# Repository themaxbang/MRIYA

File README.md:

# MRIYA
**MRIYA** (Ukrainian for «Dream») is a 42-key column-staggered split keyboard based on [Corne Cherry v.3.0.1](https://github.com/foostan/crkbd)

## Features
- Design optimized for wireless
- Updated thumb cluster (inspired by [Jian](https://github.com/KGOH/Jian-Info))
- Reset buttons
- Native nice!view support
- Updated column stagger
- 3DP bumper case (inspired by [Dao Choc BLE](https://github.com/yumagulovrn/dao-choc-ble))
- CNC plates
- BSI-10H Slide Switches
- Molex PicoBlade 1.25mm connectors
- LiPo Battery 301230/301645 support
- No-Solder Spring Headers support
- No LEDs
- Hotswap MX
- ZMK support

## PCB
<table align="center">
    <tr>
        <td align="left">Software</td>
        <td align="left"><a href="https://www.kicad.org/">KiCad 9.0.7 Stable</a></td>
    </tr>
    <tr>
        <td align="left">Silkscreen font</td>
        <td align="left"><a href="https://fonts.google.com/specimen/Roboto">Roboto</a> | <a href="https://fonts.google.com/specimen/Roboto+Condensed">Roboto condensed</a></td>
    </tr>
    <tr>
        <td align="left">Bird logo</td>
        <td align="left"><a href="https://pngtree.com/freepng/minimalist-bird-logo_4124682.html">pngtree.com</a></td>
    </tr>
    <tr>
        <td align="left">PCB Art</td>
        <td align="left"> Olga Rai <a href="https://www.shutterstock.com/g/OlgaRai">Shutterstock</a> | <a href="https://stock.adobe.com/contributor/209778624/olga-rai">Adobe Stock</a></td>
    </tr>
</table>

#### <div align="center">Top<div>
| 
 ---- | -----  

#### <div align="center">Bottom<div>
|   
 ---- | -----  

## PCB Plates
<table align="center">
    <tr>
        <td align="left">Logo font</td>
        <td align="left"><a href="https://fontbundles.net/integritype-studio/1610789-william-narasi-calligraphy-font">William Narasi</a></td>
    </tr>
</table>

|   
 ---- | -----

## 3D Printed Bumper Case
#### <div align="center">FDM<div>
|
 ---- | -----

## Bill of Materials
Reference|Name|Qty|LCSC|AliExpess
 ------- | ------- | ------- | ------- | ------- 
U1, U2 | Microcontroller: [nRFMicro](https://github.com/joric/nrfmicro) / SuperMini nRF52840 / nice!nano | 2 | --- | [AliExpress](https://aliexpress.com/item/1005006282506884.html?sku_id=12000036599296319)
SW1-SW42 | Kailh Hotswap Socket CPG151101S11 | 42 | [LCSC](https://www.lcsc.com/product-detail/Mechanical-Keyboard-Shaft_span-style-background-color-ff0-Kailh-span-CPG151101S11-16_C5156480.html) | [AliExpress](https://aliexpress.com/item/1005007639688349.html?sku_id=12000041605806628)
D1-D42 | Diode 1N4148W (SOD-123) | 42 | [LCSC](https://www.lcsc.com/product-detail/Switching-Diodes_JSMSEMI-1N4148W_C917030.html) | [AliExpess](https://aliexpress.com/item/1005008224039255.html?sku_id=12000044288109815)
PSW1, PSW2 | Power Switch SUNGMUN BSI-10H | 2 | [LCSC](https://www.lcsc.com/product-detail/Slide-Switches_SM-Switch-BSI-10H_C5775777.html) | [AliExpress](https://aliexpress.com/item/1005006561513178.html?sku_id=12000037678382032)
RSW1, RSW2 | Reset Button TC-1109-C-A (4.5x4.5x**5.5**mm) 4pin DIP | 2 | [LCSC](https://www.lcsc.com/product-detail/Tactile-Switches_XKB-Connectivity-TC-1109-C-A_C561500.html) | [AliExpress](https://aliexpress.com/item/1005001629344310.html?sku_id=12000016890022339)
J1, J2 | Nice!view display [optional] | 2 | --- | [AliExpess](https://aliexpress.com/item/1005007972384358.html?sku_id=12000043094547978)
J3, J4 | Molex PicoBlade 532610271 connector | 2 | [LCSC](https://www.lcsc.com/product-detail/Wire-To-Board-Wire-To-Wire-Connector_MOLEX-532610271_C189700.html) | [AliExpress](https://aliexpress.com/item/1005004425197503.html?sku_id=12000029142536237)
--- | Socket PH5 12pin (Female header) pitch 2.54mm | 4 | --- | [AliExpress](https://aliexpress.com/item/1005006055026707.html?sku_id=12000037525939024)
--- | Socket PH5 5pin (Female header) pitch 2.54mm | 2 | --- | [AliExpress](https://aliexpress.com/item/1005006055026707.html?sku_id=12000037525939018)
--- | LiPo Battery 301230 | 2 | --- | [AliExpress](https://aliexpress.com/item/1005008151618452.html?sku_id=12000044007992383)
--- | LiPo Battery 301645 (Mounts underneath the PCB. During assembly, you must trim the PH5 sockets and power switches legs flush with the PCB using a special template) [optional] | 2 | --- | [AliExpress](https://aliexpress.com/item/32822552643.html?sku_id=64950436890)
--- | Jst Connector 1.25mm Dual Head Wire Cable 2 Pin Female Plug [optional] | 2 | --- | [AliExpress](https://aliexpress.com/item/1005006000774395.html?sku_id=12000035250620558)
--- | Silicone Bumpers 8x2mm (for Classic case or CNC plates) | 12 | --- | [AliExpress](https://aliexpress.com/item/1005005467943079.html?sku_id=12000033199265741)
--- | Silicone Bumpers 8x1.5mm (for FR4 plates) | 12 | --- | [AliExpress](https://aliexpress.com/item/1005002478823169.html?sku_id=12000038015770755)
--- | Brass Round Standoff Spacer Female M2 10mm | 4 | --- | [AliExpress](https://aliexpress.com/item/1005002979083511.html?sku_id=12000023043529034)
--- | Brass Round Standoff Spacer Female M2 7mm | 8 | --- | [AliExpress](https://aliexpress.com/item/1005002979083511.html?sku_id=12000023043529031)
--- | Brass Round Standoff Spacer Female M2 6mm (for Classic case 301230 + FR4 plates) | 8 | --- | [AliExpress](https://aliexpress.com/item/1005002979083511.html?sku_id=12000023043529030)
--- | M3 ABS Nylon Round Standoff Spacer 3.5mm | 12 | --- | [AliExpress](https://aliexpress.com/item/1005004162177818.html?sku_id=12000028239766646)
--- | M3 Black ABS Non-Threaded Hollowed Nylon Spacer 5mm [optional] | 4 | --- | [AliExpress](https://aliexpress.com/item/1005006120526666.html?sku_id=12000035843885709)
--- | M2 Stainless Steel Torx Six-Lobe Ultra Thin Head Screw 4mm | 24 | --- | [AliExpress](https://aliexpress.com/item/1005002461101939.html?sku_id=12000025423430581)
--- | M2 Stainless Steel Torx Head Flat Countersunk Screw 8mm (for Classic case + FDM plates) | 12 | --- | [AliExpress](https://aliexpress.com/item/1005007404555871.html?sku_id=12000040603875540)
--- | M2 Stainless Steel Torx Head Flat Countersunk Screw 5mm (for Classic case + FR4 plates) | 12 | --- | [AliExpress](https://aliexpress.com/item/1005007404555871.html?sku_id=12000040603875538)
--- | M2 Grade 12.9 Insert Torx Screw 5mm (for CNC covers) [optional] | 4 | --- | [AliExpress](https://aliexpress.com/item/4000498337202.html?sku_id=10000002274132371)
--- | М2 (OD 3.2mm) Brass Thread Heat Insert (for FDM plates and covers) length 3mm | 16 | --- | [AliExpress](https://aliexpress.com/item/1005006161392792.html?sku_id=12000036051013760)

## Firmware
You can use any firmware compatible with the Corne keyboard.
[ZMK Config](https://github.com/themaxbang/mriya-zmk-config) for the MRIYA

## Inspiration
- [Corne](https://github.com/foostan/crkbd) | [Corne Ultralight](https://github.com/petejohanson/crkbd/tree/board/corne-ultralight)
- [Jian](https://github.com/KGOH/Jian-Info)
- [Chocofi](https://github.com/pashutk/chocofi) | [Fifi](https://github.com/raychengy/fifi_split_keeb)
- [Dao Choc BLE](https://github.com/yumagulovrn/dao-choc-ble)

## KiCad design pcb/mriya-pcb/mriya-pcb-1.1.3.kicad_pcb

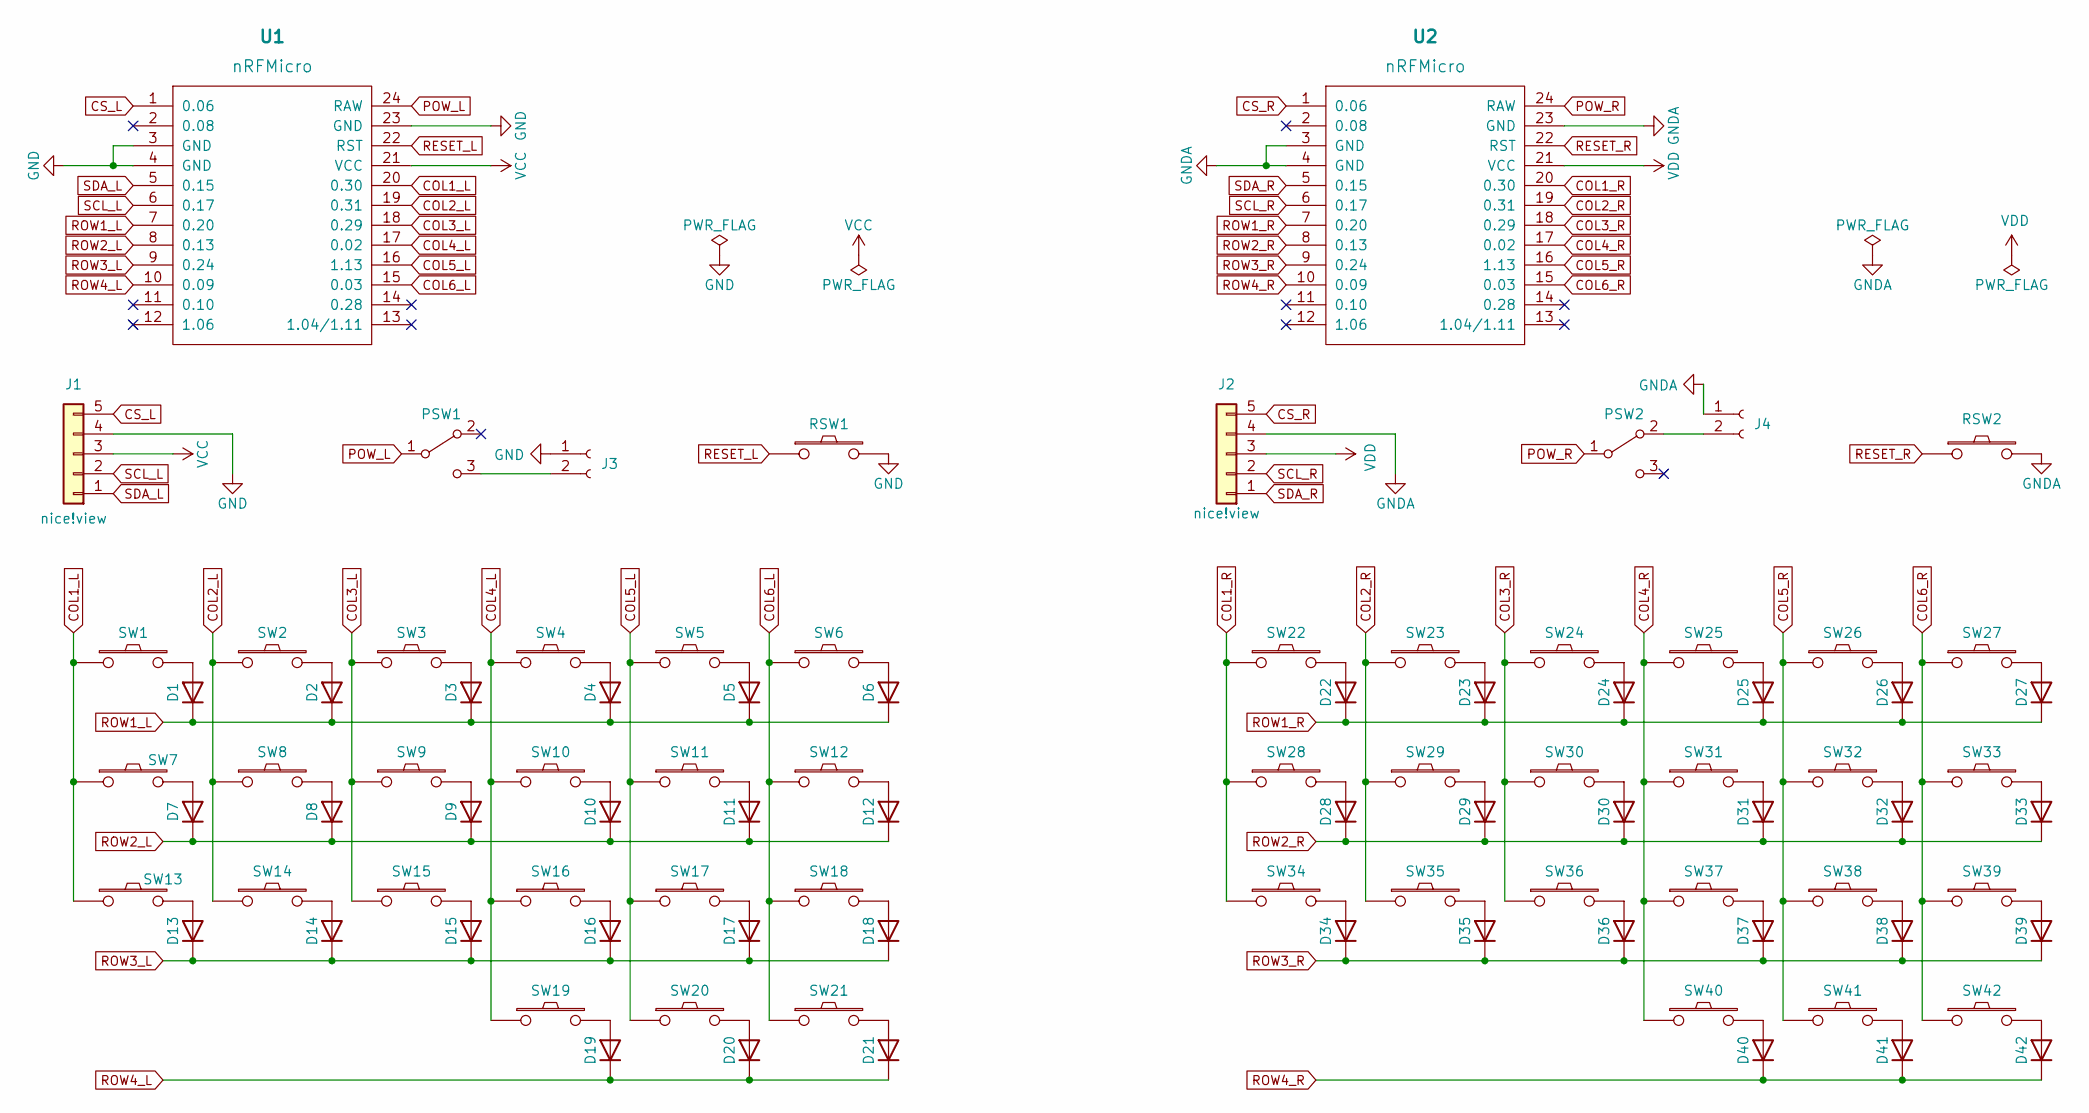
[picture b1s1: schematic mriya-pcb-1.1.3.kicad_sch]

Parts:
D1, D2, D3, D4, D5, D6, D7, D8, D9, D10, D11, D12, D13, D14, D15, D16, D17, D18, D19, D20, D21, D22, D23, D24, D25, D26, D27, D28, D29, D30, D31, D32, D33, D34, D35, D36, D37, D38, D39, D40, D41, D42: D; 1N4148_T4
J1, J2: nice!view; nice_view
J3, J4: JST; Molex_532610271
PSW1, PSW2: SW_SPDT; BSI-10h
RSW1, RSW2: RSW; RSW_4.5x4.5_left
SW1, SW2, SW3, SW4, SW5, SW6, SW7, SW8, SW9, SW10, SW11, SW12, SW13, SW14, SW15, SW16, SW17, SW18, SW19, SW20, SW21, SW22, SW23, SW24, SW25, SW26, SW27, SW28, SW29, SW30, SW31, SW32, SW33, SW34, SW35, SW36, SW37, SW38, SW39, SW40, SW41, SW42: SW_PUSH; CherryMX_Hotswap_1U
U1, U2: nRFMicro; nRFMicro_v2

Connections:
COL1_L: SW1.1, SW7.1, SW13.1, U1.20 (0.30)
COL1_R: SW22.1, SW28.1, SW34.1, U2.20 (0.30)
COL2_L: SW2.1, SW8.1, SW14.1, U1.19 (0.31)
COL2_R: SW23.1, SW29.1, SW35.1, U2.19 (0.31)
COL3_L: SW3.1, SW9.1, SW15.1, U1.18 (0.29)
COL3_R: SW24.1, SW30.1, SW36.1, U2.18 (0.29)
COL4_L: SW4.1, SW10.1, SW16.1, SW19.1, U1.17 (0.02)
COL4_R: SW25.1, SW31.1, SW37.1, SW40.1, U2.17 (0.02)
COL5_L: SW5.1, SW11.1, SW17.1, SW20.1, U1.16 (1.13)
COL5_R: SW26.1, SW32.1, SW38.1, SW41.1, U2.16 (1.13)
COL6_L: SW6.1, SW12.1, SW18.1, SW21.1, U1.15 (0.03)
COL6_R: SW27.1, SW33.1, SW39.1, SW42.1, U2.15 (0.03)
CS_L: J1.5, U1.1 (0.06)
CS_R: J2.5, U2.1 (0.06)
GND: J1.4, J3.1 (Pin_2), RSW1.2, U1.3 (GND), U1.4 (GND), U1.23 (GND)
GNDA: J2.4, J4.1 (Pin_2), RSW2.2, U2.3 (GND), U2.4 (GND), U2.23 (GND)
unnamed: D1.2 (A), SW1.2
unnamed: D2.2 (A), SW2.2
unnamed: D3.2 (A), SW3.2
unnamed: D4.2 (A), SW4.2
unnamed: D5.2 (A), SW5.2
unnamed: D6.2 (A), SW6.2
unnamed: D7.2 (A), SW7.2
unnamed: D8.2 (A), SW8.2
unnamed: D9.2 (A), SW9.2
unnamed: D10.2 (A), SW10.2
unnamed: D11.2 (A), SW11.2
unnamed: D12.2 (A), SW12.2
unnamed: D13.2 (A), SW13.2
unnamed: D14.2 (A), SW14.2
unnamed: D15.2 (A), SW15.2
unnamed: D16.2 (A), SW16.2
unnamed: D17.2 (A), SW17.2
unnamed: D18.2 (A), SW18.2
unnamed: D19.2 (A), SW19.2
unnamed: D20.2 (A), SW20.2
unnamed: D21.2 (A), SW21.2
unnamed: D22.2 (A), SW22.2
unnamed: D23.2 (A), SW23.2
unnamed: D24.2 (A), SW24.2
unnamed: D25.2 (A), SW25.2
unnamed: D26.2 (A), SW26.2
unnamed: D27.2 (A), SW27.2
unnamed: D28.2 (A), SW28.2
unnamed: D29.2 (A), SW29.2
unnamed: D30.2 (A), SW30.2
unnamed: D31.2 (A), SW31.2
unnamed: D32.2 (A), SW32.2
unnamed: D33.2 (A), SW33.2
unnamed: D34.2 (A), SW34.2
unnamed: D35.2 (A), SW35.2
unnamed: D36.2 (A), SW36.2
unnamed: D37.2 (A), SW37.2
unnamed: D38.2 (A), SW38.2
unnamed: D39.2 (A), SW39.2
unnamed: D40.2 (A), SW40.2
unnamed: D41.2 (A), SW41.2
unnamed: D42.2 (A), SW42.2
unnamed: J3.2 (Pin_1), PSW1.3 (C)
unnamed: J4.2 (Pin_1), PSW2.2 (A)
POW_L: PSW1.1 (B), U1.24 (RAW)
POW_R: PSW2.1 (B), U2.24 (RAW)
RESET_L: RSW1.1, U1.22 (RST)
RESET_R: RSW2.1, U2.22 (RST)
ROW1_L: D1.1 (K), D2.1 (K), D3.1 (K), D4.1 (K), D5.1 (K), D6.1 (K), U1.7 (0.20)
ROW1_R: D22.1 (K), D23.1 (K), D24.1 (K), D25.1 (K), D26.1 (K), D27.1 (K), U2.7 (0.20)
ROW2_L: D7.1 (K), D8.1 (K), D9.1 (K), D10.1 (K), D11.1 (K), D12.1 (K), U1.8 (0.13)
ROW2_R: D28.1 (K), D29.1 (K), D30.1 (K), D31.1 (K), D32.1 (K), D33.1 (K), U2.8 (0.13)
ROW3_L: D13.1 (K), D14.1 (K), D15.1 (K), D16.1 (K), D17.1 (K), D18.1 (K), U1.9 (0.24)
ROW3_R: D34.1 (K), D35.1 (K), D36.1 (K), D37.1 (K), D38.1 (K), D39.1 (K), U2.9 (0.24)
ROW4_L: D19.1 (K), D20.1 (K), D21.1 (K), U1.10 (0.09)
ROW4_R: D40.1 (K), D41.1 (K), D42.1 (K), U2.10 (0.09)
SCL_L: J1.2, U1.6 (0.17)
SCL_R: J2.2, U2.6 (0.17)
SDA_L: J1.1, U1.5 (0.15)
SDA_R: J2.1, U2.5 (0.15)
VCC: J1.3, U1.21 (VCC)
VDD: J2.3, U2.21 (VCC)

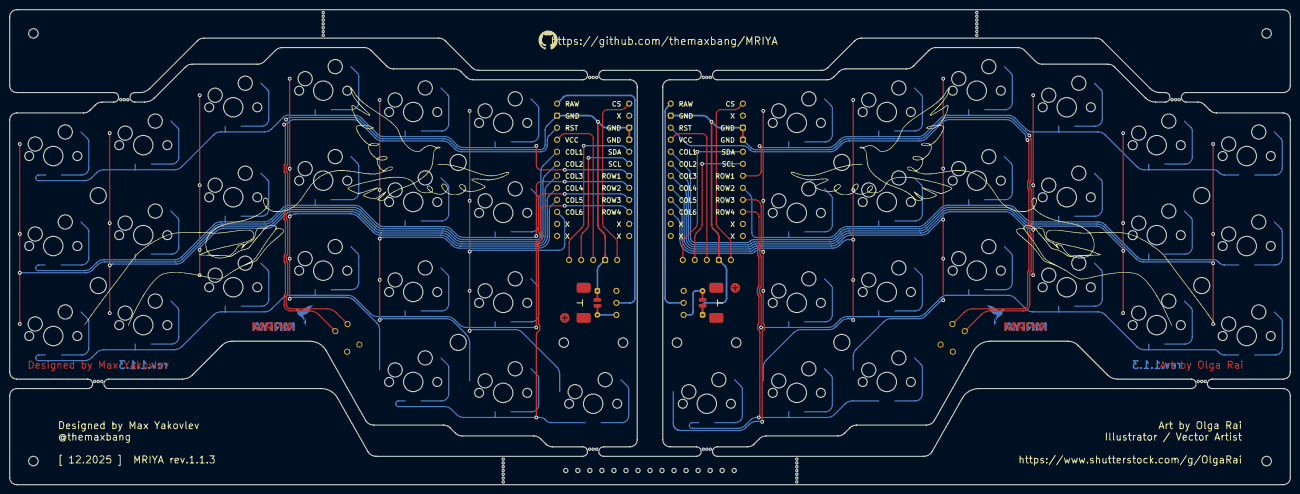
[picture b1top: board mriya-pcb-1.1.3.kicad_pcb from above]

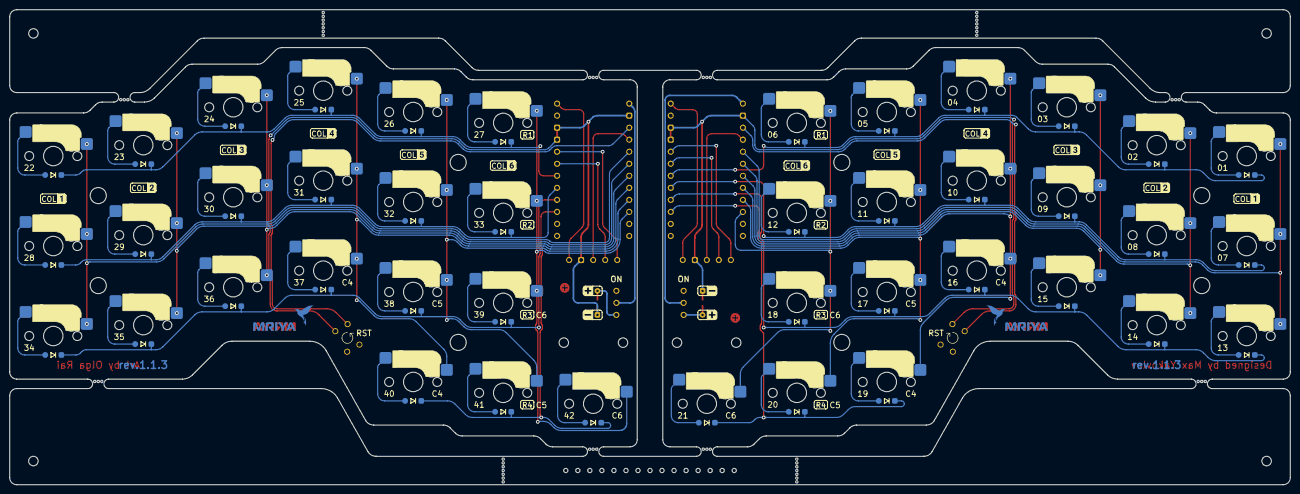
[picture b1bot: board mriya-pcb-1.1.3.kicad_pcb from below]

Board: 2 copper layers, 270.4 x 100.3 mm, 140 parts (46 on the bottom side), 78 nets.

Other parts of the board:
Bird_Hand_Left: ART; Bird_Hand_Left
Bird_Hand_Right: ART; Bird_Hand_Right
Bird_Logo_B.Cu_Left: LOGO; Bird_Logo_B.Cu_Left
Bird_Logo_B.Cu_Right: LOGO; Bird_Logo_B.Cu_Right
Bird_Logo_B.Mask_Left: LOGO; Bird_Logo_B.Mask_Left
Bird_Logo_B.Mask_Right: LOGO; Bird_Logo_B.Mask_Right
H: Holes 0.9mm; Сutting_template
H1, H2, H11, H12: Hole 2mm; Hole_2mm
H3, H4, H5, H6, H7, H8, H9, H10: Hole 3.4mm; Hole_3.4mm
LOGO: LOGO; GitHub_logo
MB1, MB2, MB3, MB4: MB; Mouse_Bite
MB-2mm-1, MB-2mm-2, MB-2mm-3, MB-2mm-4, MB-2mm-5, MB-2mm-6, MB-2mm-7, MB-2mm-8: MB; Mouse_Bite_2mm_v1
MH1, MH2, MH3, MH4: MountingHole 2mm; Mounting_Hole_2mm
MRIYA_Logo_B.Cu, MRIYA_Logo_B.Cu#2: LOGO; Mriya_Logo_F.Cu
MRIYA_Logo_B.Mask, MRIYA_Logo_B.Mask#2: LOGO; Mriya_Logo_F.Mask
MRIYA_Logo_F.Cu, MRIYA_Logo_F.Cu#2: LOGO; Mriya_Logo_F.Cu
MRIYA_Logo_F.Mask, MRIYA_Logo_F.Mask#2: LOGO; Mriya_Logo_F.Mask
OH1, OH2: Oval Hole; Oval_Hole

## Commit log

2023-04-26 pictures
2023-04-26 added logo picture
2023-04-26 added kicad files
2023-04-26 Create LICENSE
2023-04-28 renders
2023-04-28 links
2023-04-29 added renders
2023-04-29 updated references
2023-05-08 updated renders
2024-01-30 update redme
2024-02-04 update renders
2024-07-14 added a 3DP Case
2024-07-21 update 3DP case
2024-08-03 update 3DP cases
2024-08-03 update SLA case
2024-08-14 update FDM case
2024-08-15 update cases
2024-08-18 update MJF case
2024-08-18 update FDM bumper case
2024-08-18 update SLA and MJF cases
2024-08-22 update FDM cases
2024-08-22 update .stl files
2024-08-28 update SLA&MJF cases
2024-09-17 update MJF&SLA cases
2024-09-22 update bumper cases
2024-10-31 update FDM classic case
2025-01-19 update PCB renders
2025-03-17 update CNC plates
2025-04-25 update MJF bumper case
2025-04-30 update BOM
2025-11-23 update case files
2025-12-15 add gerbers
2026-02-08 add kicad files
2026-02-08 add pictures
